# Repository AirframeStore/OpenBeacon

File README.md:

# OpenBeacon Project
An open source synchronized beacon light for experimental aircraft by [Airframe.Store](https://www.airframe.store)

## Open Source Data and Sale
Everything needed to build an OpenBeacon Device will be made publicly available at no cost: PCB Schematics and Layouts, Source Code, BOMs, 3d Models, drawings for manufacturing and build manuals.  
Not everybody has access to a personal PCB making machine, so we are planning to sell partial or full kits at the [Airframe Online Store](https://www.airframe.store) in several stages of completeness:  
- Plans only (as mentionned above) at no cost (forever!)
- Bare PCB only (all other components must be aquired seperatly, also soldering and programming must be done) at tiny cost
- PCB + components (must still be soldered and programmed by the user) at little cost
- Fully assembled and programmed PCB at medium cost, below most (or all?) available COTS devices

## Motivation
The goal is to develop an open source beacon light pcb that can be used wherever no "Form 1" is needed to exchange costly COTS components with self-made hardware.

## Modularity
Some OpenBeacon Devices like the OB3k are modular, so that users can choose either a light and low profile beacon or a stacked version of two or more OB3k PCBs if more visibility is desired. The entire system of blinking lights is also modular, lights can be added or removed and the rest will keep blinking in sync. This also applies to devices removed (or destroyed?) during runtime.

## Synchronized
There's nothing aesthetically worse than anti-collision lights and beacons flashing all over the place on an aircraft.  
OpenBeacon share a masterless automatic sync-bus, so that all lights flash beautifully in sync. This function is implemented into all devices and works no matter how many OpenBeacon devices are connected, even if devices are connected or disconnected during runtime.

### OpenBeacon Frame
The OpenBeacon blinking patterns are programmed so that they all fit within one (or a whole-numbered fraction of one) OpenBeacon Frame that is 3000 ms long. When powered up, each device will start blinking in its uniquely programmed pattern that repeats every 3000 ms. When a sync pulse appears on the sync bus, the pattern restarts.

### Standard Patterns
Standard Patterns include:  
Beacon: 750 ms on, 2250 ms off  
ACL: 50 ms on, 100 ms off, 50 ms on, 1300 ms off (x2)  
WigWag: 1500 ms on, 1500 ms off (or vice versa for the wigwag partner light)  

### Custom Patterns
programming TBD

### Open-Collector Sync-Line
OpenBeacon uses an open-collector Sync-Bus where all participants are equals. Everytime a bus participant finishes its blink pattern it pulls the sync bus low to send a sync pulse to all bus members. With all devices counting a tiiiiny bit differently, the fastest member to reach the end of its blink frame sends the pulse. If the fastest member is removed from the bus, the second fastest takes its job:  
After a Frame is completed, the device will pull the sync bus low for 2 ms causing all devices that are listening on the bus to restart their frame. Since the bus is an open-collector bus, all devices can equally pull the bus low, without damaging one another. Also, since all bus participants evaluate if the bus is already low before pulling low, simultaneous low-pulling is unlikely.

## Devices
### Beacon OB3k
  
The OpenBeacon 3k is a cylindrical stackable low profile Beacon light. The PCB has 20 powerful red [Side View LEDs by Würth Elektronik](https://www.we-online.com/de/components/products/led/leds/color_led/chip_led_side_view),  10 on the top layer spaced 36° appart and 10 on the bottom layer spaced 18° from the top LEDs. 
### Programmable Blink Cycles
The following are recommendations but with OpenBeacon, individual blink patterns can be programmed into each device.
#### Anti Collision Lights (ACL)
ACLs, often white at the wing tips, rear, top and/or bottom give short flashes. They usually blink in a "blink-blink pause" sequence that repeats every 1.5 seconds. This pattern fits twice in a standard OpenBeacon frame.
#### Beacons
Beacons, most often red lights on the top or bottom of the fuselage, usually have a longer on-time than ACLs. They can blink in sync or shifted by half a phase from the ACLs. They usually have a 25-50% on-time over a OpenBeacon half-frame.
#### WigWag Blinking Lights
WigWag Lights are often used in forward pointing lights to increase heads-on visibility with a bright white light. The WigWag pattern (lights jumping left to right) further increase visibility. Two WigWag lights usually turn on back and forth each at 50% of a full OpenBeacon Frame, so that the Light jumps to the other side every 1.5 seconds.

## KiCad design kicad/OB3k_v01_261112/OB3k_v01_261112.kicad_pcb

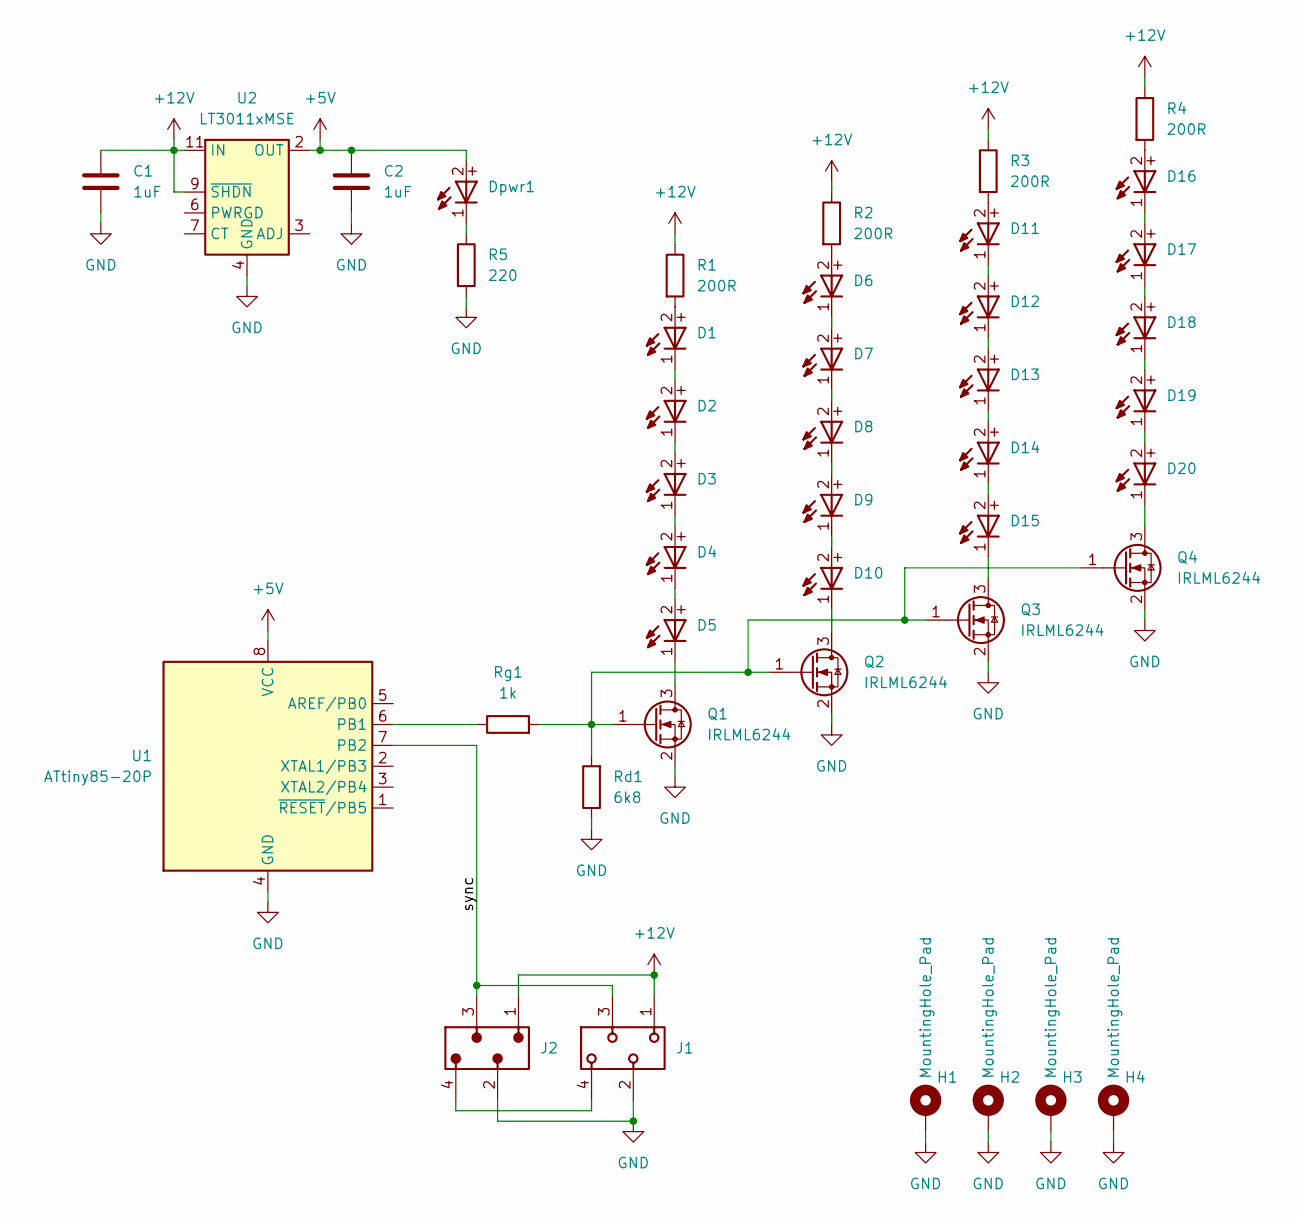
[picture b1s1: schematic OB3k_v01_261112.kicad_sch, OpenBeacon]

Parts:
C1, C2: 1uF; C_1206_3216Metric_Pad1.33x1.80mm_HandSolder
D1, D2, D3, D4, D5, D6, D7, D8, D9, D10, D11, D12, D13, D14, D15, D16, D17, D18, D19, D20: 1204_155124RS73200; D_Wurth_WL-SMSW-1204; Part Number 155124RS73200
Dpwr1: 1204_155124RS73200; D_0603_1608Metric; Part Number 155124RS73200
H1: MountingHole_Pad
H2, H3, H4: MountingHole_Pad; MountingHole_3.2mm_M3_Pad_TopBottom
J1: 690367180472; J_Wurth_WR-MM_690367180472; Working Voltage (V (AC)) 250
J2: 690357100472; J_Wurth_WR-MM_690357100472
Q1, Q2, Q3, Q4: IRLML6244; SOT-23
R1, R2, R3, R4: 200R; R_0805_2012Metric
R5: 220; R_0805_2012Metric
Rd1: 6k8; R_0805_2012Metric
Rg1: 1k; R_0805_2012Metric
U1: ATtiny85-20P; DIP-8_W7.62mm
U2: LT3011xMSE; MSOP-12-1EP_3x4.039mm_P0.65mm_EP1.651x2.845mm

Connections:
+5V: C2.1, Dpwr1.2 (+), U1.8 (VCC), U2.2 (OUT)
+12V: C1.1, J1.1, J2.1, R1.1, R2.1, R3.1, R4.1, U2.9 (~SHDN), U2.11 (IN)
/sync: J1.3, J2.3, U1.7 (PB2)
GND: C1.2, C2.2, H1.1 (1_1), H2.1 (1_1), H3.1 (1_1), H4.1 (1_1), J1.2, J2.2, Q1.2 (S), Q2.2 (S), Q3.2 (S), Q4.2 (S), R5.2, Rd1.1, U1.4 (GND), U2.4 (GND), U2.13 (GND)
unnamed: D1.2 (+), R1.2
unnamed: D1.1 (-), D2.2 (+)
unnamed: D2.1 (-), D3.2 (+)
unnamed: D3.1 (-), D4.2 (+)
unnamed: D4.1 (-), D5.2 (+)
unnamed: D5.1 (-), Q1.3 (D)
unnamed: D6.2 (+), R2.2
unnamed: D6.1 (-), D7.2 (+)
unnamed: D7.1 (-), D8.2 (+)
unnamed: D8.1 (-), D9.2 (+)
unnamed: D9.1 (-), D10.2 (+)
unnamed: D10.1 (-), Q2.3 (D)
unnamed: D11.2 (+), R3.2
unnamed: D11.1 (-), D12.2 (+)
unnamed: D12.1 (-), D13.2 (+)
unnamed: D13.1 (-), D14.2 (+)
unnamed: D14.1 (-), D15.2 (+)
unnamed: D15.1 (-), Q3.3 (D)
unnamed: D16.2 (+), R4.2
unnamed: D16.1 (-), D17.2 (+)
unnamed: D17.1 (-), D18.2 (+)
unnamed: D18.1 (-), D19.2 (+)
unnamed: D19.1 (-), D20.2 (+)
unnamed: D20.1 (-), Q4.3 (D)
unnamed: Dpwr1.1 (-), R5.1
unnamed: J1.4, J2.4
unnamed: Q1.1 (G), Q2.1 (G), Q3.1 (G), Q4.1 (G), Rd1.2, Rg1.2
unnamed: Rg1.1, U1.6 (PB1)

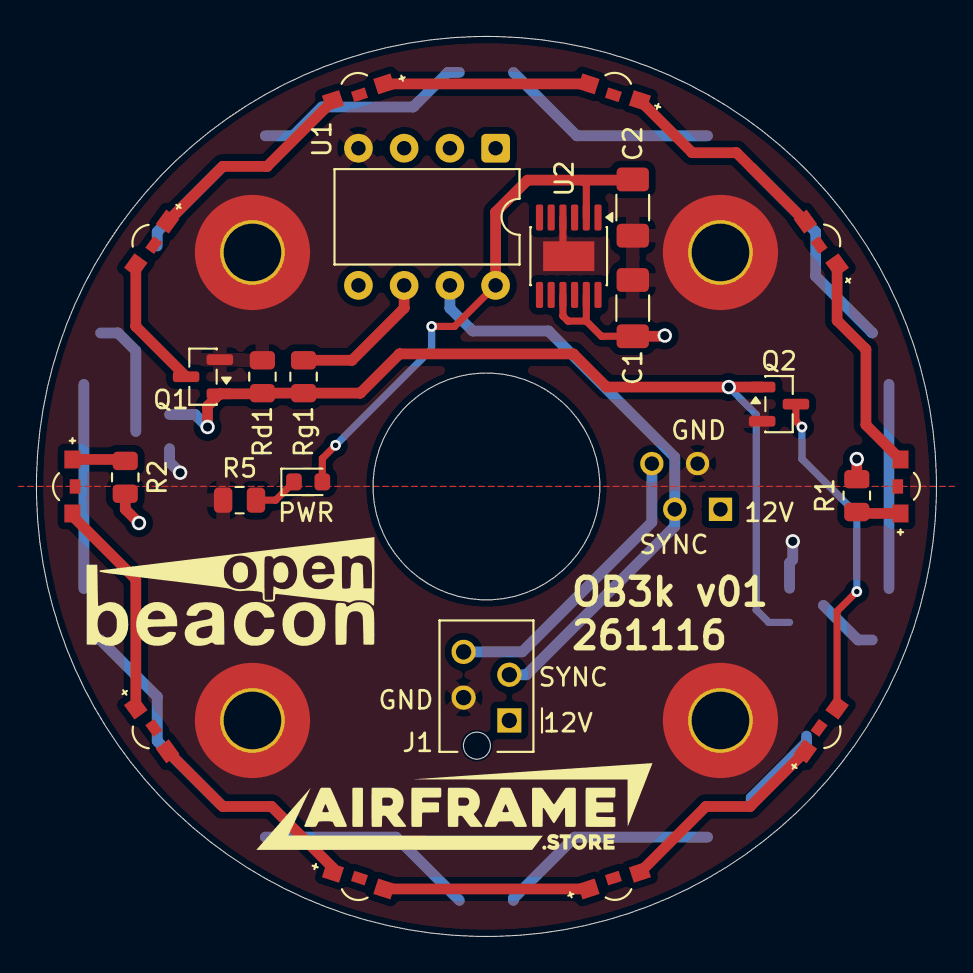
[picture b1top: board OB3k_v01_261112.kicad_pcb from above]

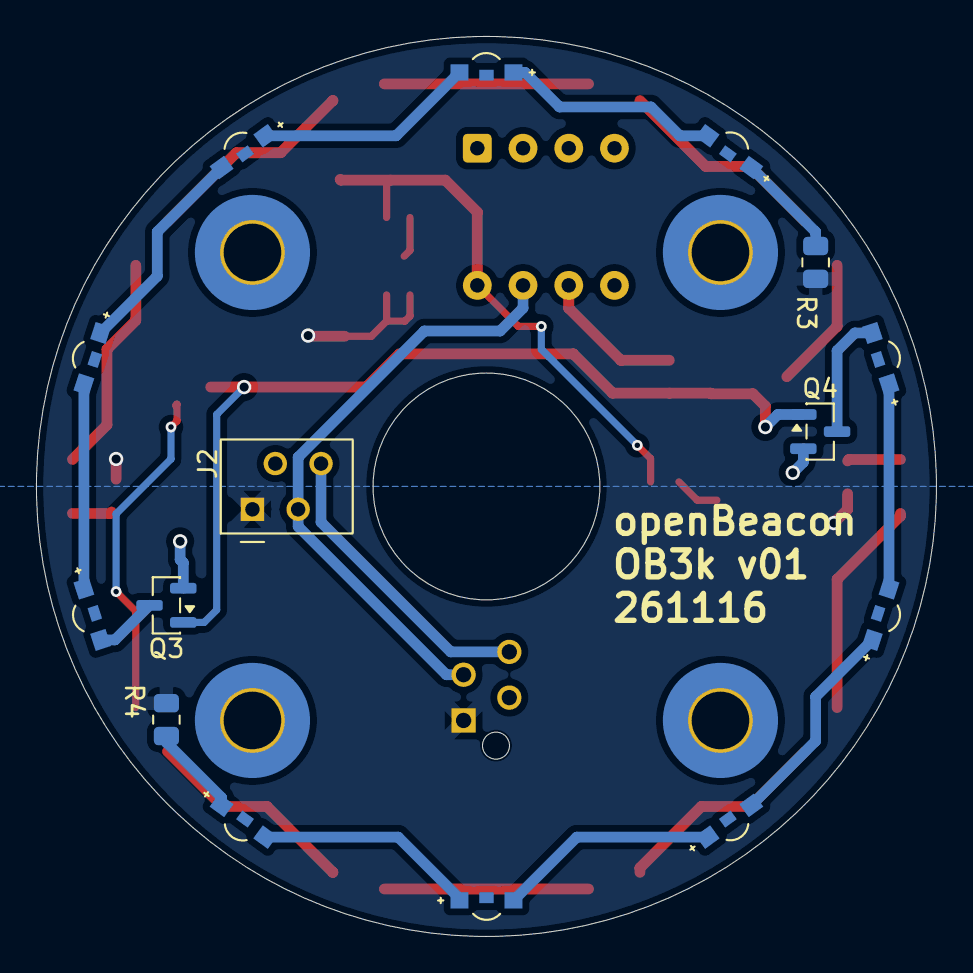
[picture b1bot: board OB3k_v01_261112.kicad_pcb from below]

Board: 2 copper layers, 50.0 x 50.0 mm, 42 parts (15 on the bottom side), 32 nets.
